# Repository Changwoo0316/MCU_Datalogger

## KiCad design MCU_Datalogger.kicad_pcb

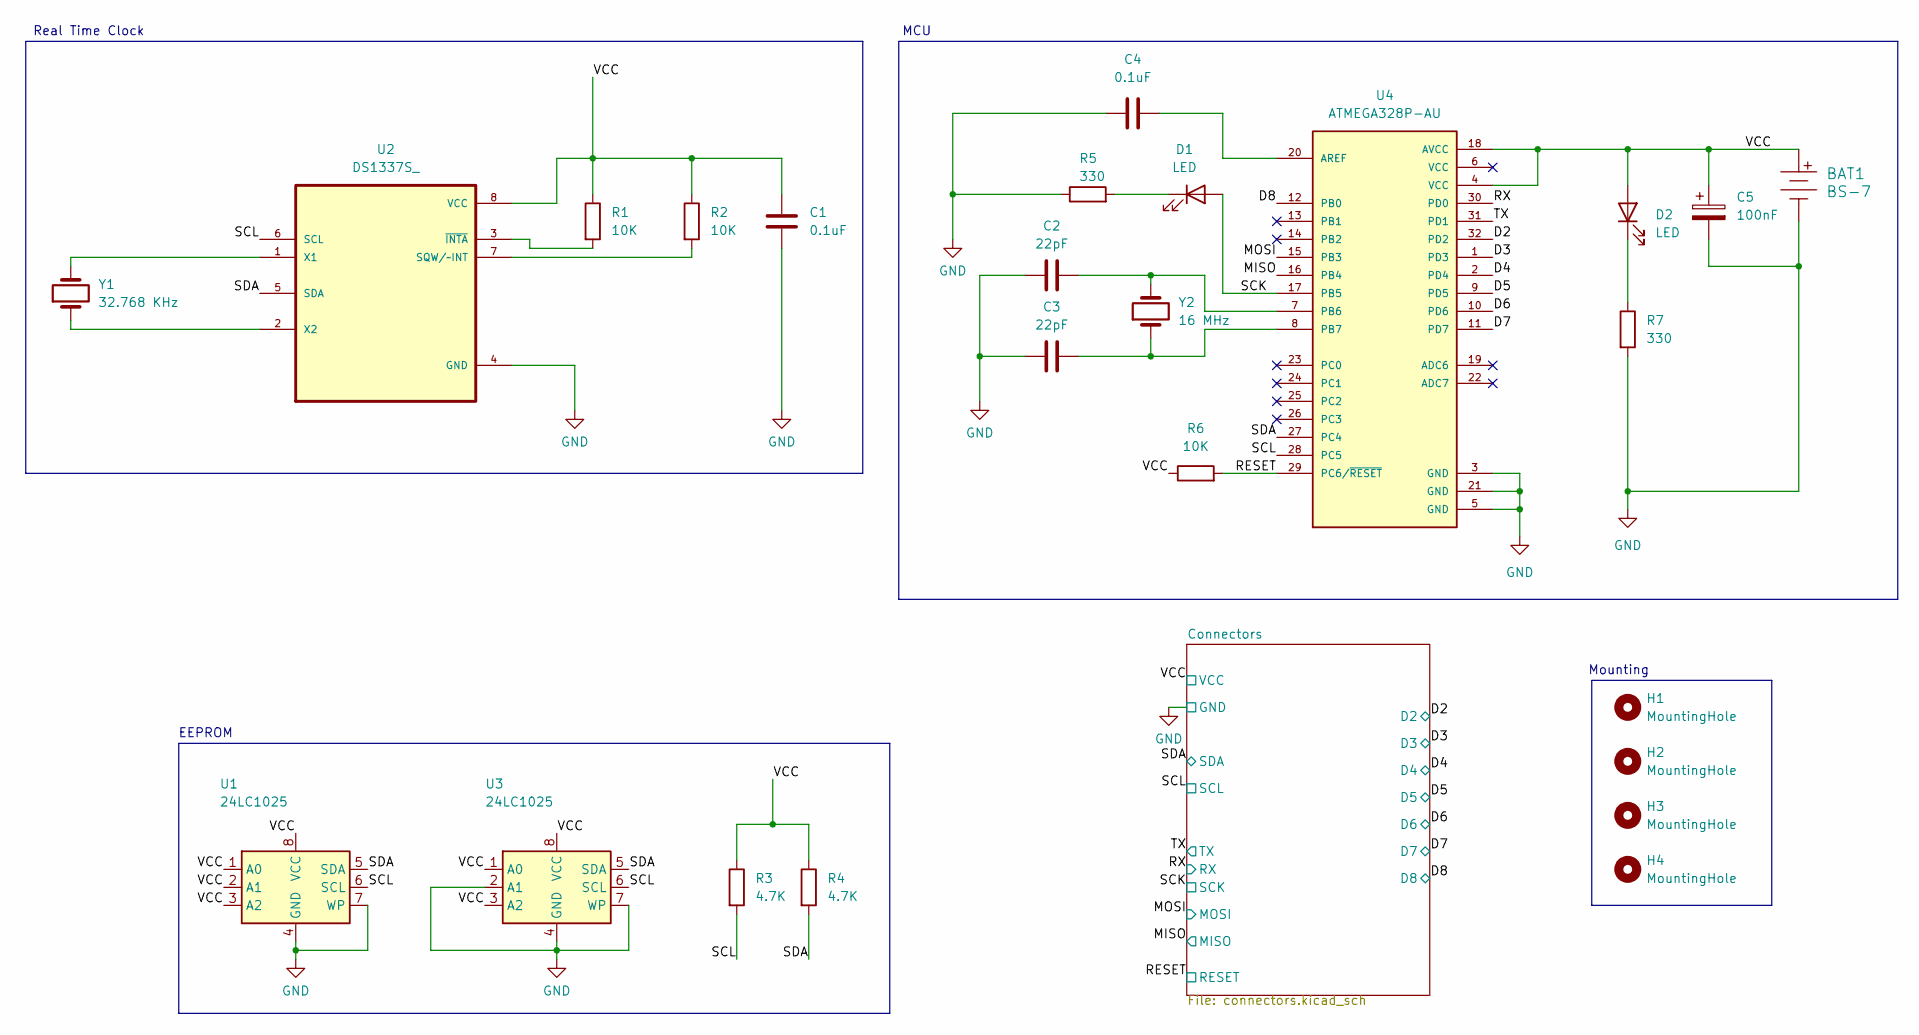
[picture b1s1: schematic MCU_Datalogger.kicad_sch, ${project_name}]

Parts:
BAT1: BS-7; PinHeader_1x02_P2.54mm_Vertical; MPN BS-7; Digi-Key_PN BS-7-ND
C1, C4: 0.1uF; C_0805_2012Metric
C2, C3: 22pF; C_0805_2012Metric
C5: 100nF; C_0805_2012Metric
D1, D2: LED; LED_0805_2012Metric
H1, H2, H3, H4: MountingHole; MountingHole_2.1mm
R1, R2, R6: 10K; R_0805_2012Metric
R3, R4: 4.7K; R_0805_2012Metric
R5, R7: 330; R_0805_2012Metric
U1, U3: 24LC1025; SOIC-8_5.23x5.23mm_P1.27mm
U2: DS1337S_; DS1337S
U4: ATMEGA328P-AU; PARTREV 8271A; DigiKey_Part_Number ATMEGA328P-AU-ND
Y1: 32.768 KHz; Crystal_SMD_5032-2Pin_5.0x3.2mm_HandSoldering
Y2: 16 MHz; Crystal_SMD_5032-2Pin_5.0x3.2mm_HandSoldering

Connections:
/D2: U4.32 (PD2); also elsewhere on the board
/D3: U4.1 (PD3); also elsewhere on the board
/D4: U4.2 (PD4); also elsewhere on the board
/D5: U4.9 (PD5); also elsewhere on the board
/D6: U4.10 (PD6); also elsewhere on the board
/D7: U4.11 (PD7); also elsewhere on the board
/D8: U4.12 (PB0); also elsewhere on the board
/MISO: U4.16 (PB4); also elsewhere on the board
/MOSI: U4.15 (PB3); also elsewhere on the board
/RESET: R6.2, U4.29 (PC6/~RESET); also elsewhere on the board
/RX: U4.30 (PD0); also elsewhere on the board
/SCK: D1.2 (A), U4.17 (PB5); also elsewhere on the board
/SCL: R3.2, U1.6 (SCL), U2.6 (SCL), U3.6 (SCL), U4.28 (PC5); also elsewhere on the board
/SDA: R4.2, U1.5 (SDA), U2.5 (SDA), U3.5 (SDA), U4.27 (PC4); also elsewhere on the board
/TX: U4.31 (PD1); also elsewhere on the board
/VCC: BAT1.1, C1.1, C5.1, D2.2 (A), R1.1, R2.1, R3.1, R4.1, R6.1, U1.1 (A0), U1.2 (A1), U1.3 (A2), U1.8 (VCC), U2.8 (VCC), U3.1 (A0), U3.3 (A2), U3.8 (VCC), U4.4 (VCC), U4.18 (AVCC); also elsewhere on the board
GND: BAT1.2, C1.2, C2.1, C3.1, C4.1, C5.2, R5.1, R7.2, U1.4 (GND), U1.7 (WP), U2.4 (GND), U3.2 (A1), U3.4 (GND), U3.7 (WP), U4.3 (GND), U4.5 (GND), U4.21 (GND); also elsewhere on the board
unnamed: D1.1 (K), R5.2
unnamed: D2.1 (K), R7.1
unnamed: R2.2, U2.7 (SQW/~INT)
unnamed: U2.1 (X1), Y1.2
unnamed: U2.2 (X2), Y1.1
unnamed: R1.2, U2.3 (~INTA)
unnamed: C4.2, U4.20 (AREF)
unnamed: C2.2, U4.7 (PB6), Y2.2
unnamed: C3.2, U4.8 (PB7), Y2.1

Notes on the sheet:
Real Time Clock
EEPROM
Mounting
MCU

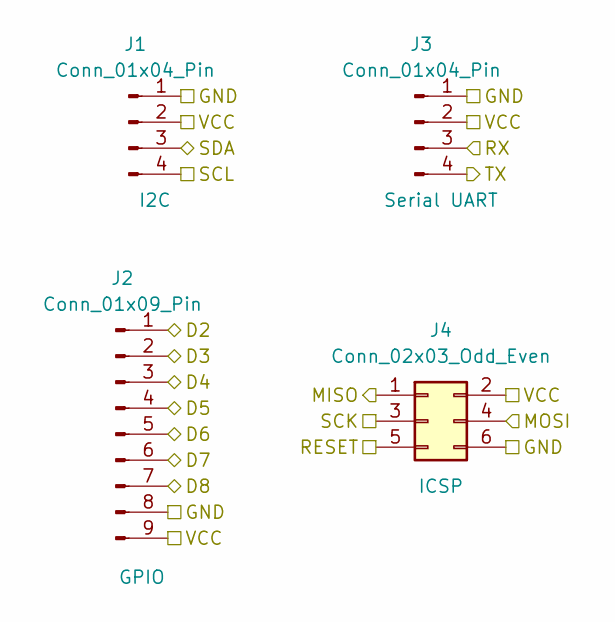
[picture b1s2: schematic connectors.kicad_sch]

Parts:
J1, J3: Conn_01x04_Pin; PinHeader_1x04_P2.54mm_Vertical
J2: Conn_01x09_Pin; PinHeader_1x09_P2.54mm_Vertical
J4: Conn_02x03_Odd_Even; PinHeader_2x03_P2.54mm_Vertical

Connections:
/D2: J2.1; also elsewhere on the board
/D3: J2.2; also elsewhere on the board
/D4: J2.3; also elsewhere on the board
/D5: J2.4; also elsewhere on the board
/D6: J2.5; also elsewhere on the board
/D7: J2.6; also elsewhere on the board
/D8: J2.7; also elsewhere on the board
/MISO: J4.1; also elsewhere on the board
/MOSI: J4.4; also elsewhere on the board
/RESET: J4.5; also elsewhere on the board
/RX: J3.3; also elsewhere on the board
/SCK: J4.3; also elsewhere on the board
/SCL: J1.4; also elsewhere on the board
/SDA: J1.3; also elsewhere on the board
/TX: J3.4; also elsewhere on the board
/VCC: J1.2, J2.9, J3.2, J4.2; also elsewhere on the board
GND: J1.1, J2.8, J3.1, J4.6; also elsewhere on the board

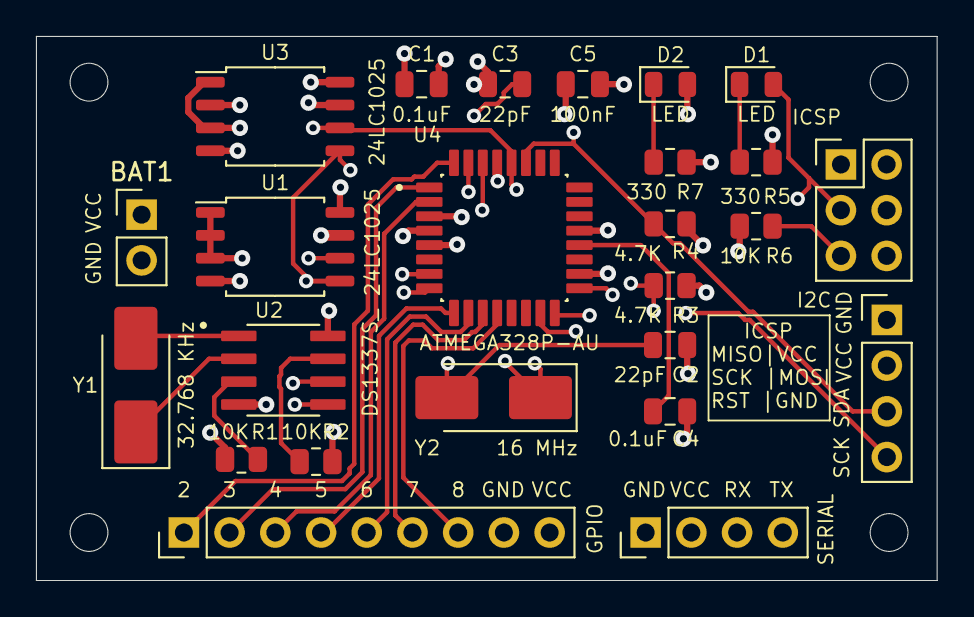
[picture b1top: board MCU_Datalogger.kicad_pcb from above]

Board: 4 copper layers, 50.0 x 30.2 mm, 29 parts (0 on the bottom side), 26 nets.

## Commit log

2025-10-24 First commit of new project
2025-10-24 Setup of EEschema for new project
2025-10-27 Have added required symbols to the schematic sheets
2025-10-27 Changed locations of symbols(arrange).
2025-10-27 Added component values
2025-10-29 Completed wiring of main sheet.
2025-10-29 Completed wiring in the second sheet.
2025-10-29 Allocated GND and VCC nets to the Power net class.
2025-10-29 Completed comments.
2025-10-29 Setup Pcbnew.
2025-10-29 Setup2 Pcbnew.
2025-10-29 Completed placement of footprints.
2025-10-29 Routing sans GND VCC complete.
2025-10-30 Completed routing.
2025-10-30 Completed the Design.
2025-10-30 Completed 2-layer PCB project.
2025-10-30 Added gerber directories to gitignore.
2025-10-30 Completed 4-layer pcb routing.
2025-10-31 Finish the 4layer PCB Project.
2025-10-31 Added gitattributes file to ignore PCB files during merge.
2025-10-31 Fixed two defects in the schematic.
2025-10-31 Fixed all defects.
